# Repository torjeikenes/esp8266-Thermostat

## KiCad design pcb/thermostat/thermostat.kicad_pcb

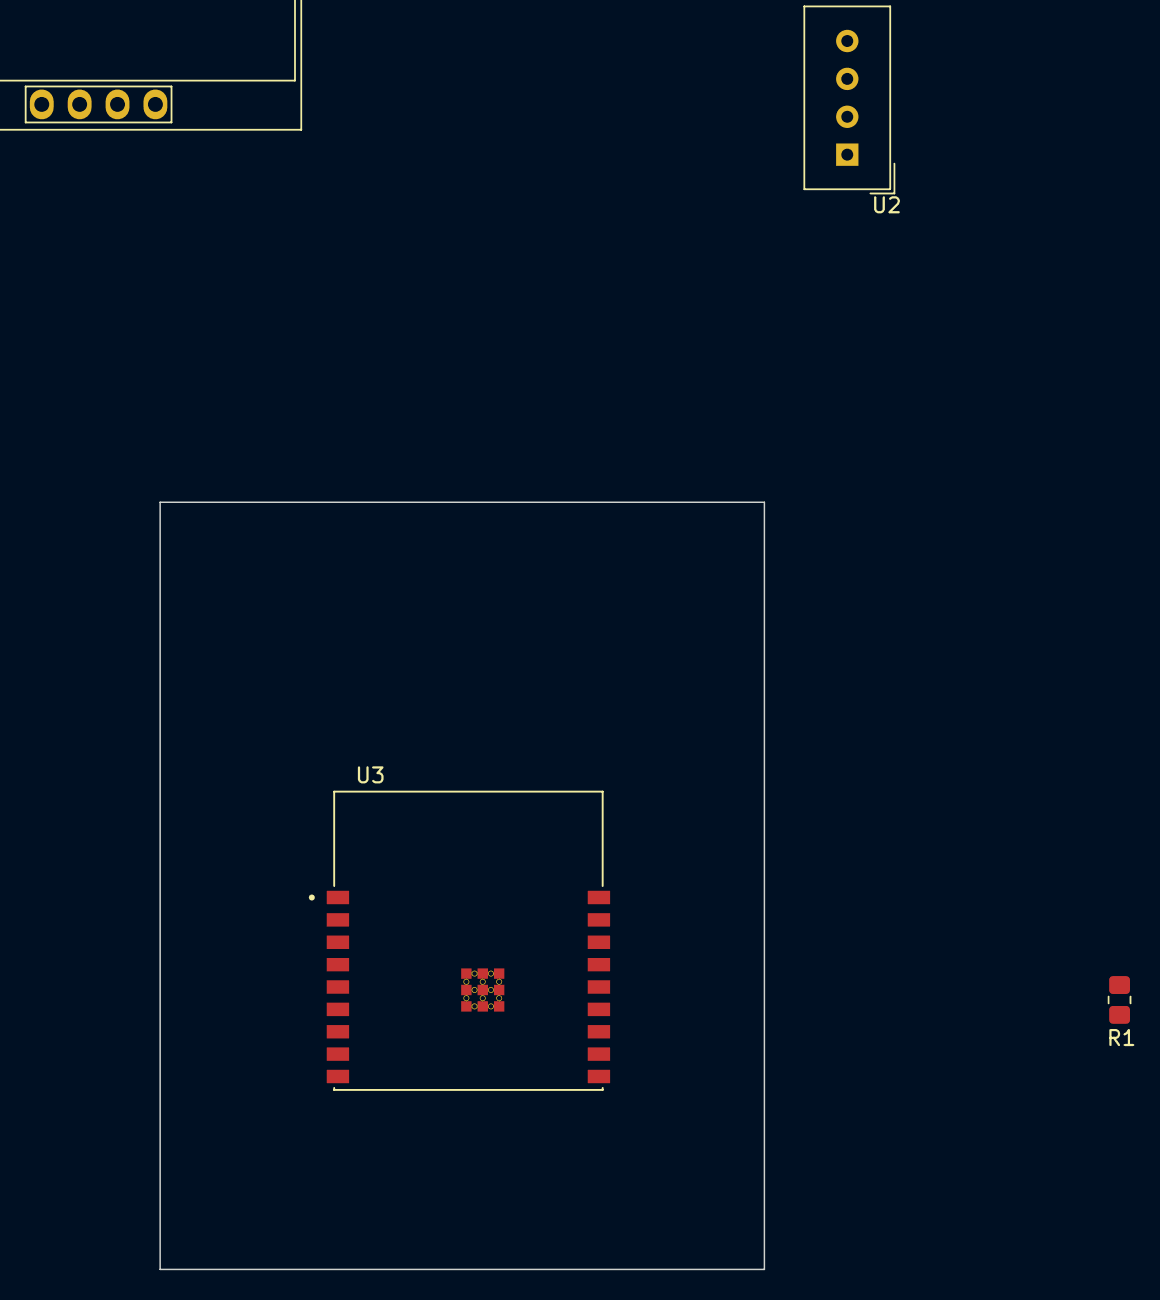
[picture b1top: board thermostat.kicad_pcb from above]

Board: 2 copper layers, 40.5 x 51.4 mm, 4 parts (0 on the bottom side), 5 nets, no tracks yet.

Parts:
Brd1: SSD1306; 128x64OLED
R1: 10k; R_0805_2012Metric_Pad1.20x1.40mm_HandSolder
U2: DHT11; Aosong_DHT11_5.5x12.0_P2.54mm
U3: ESP32-C3-WROOM-02-H4; MODULE_ESP32-C3-WROOM-02-H4

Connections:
+3V3: Brd1.2 (VCC), R1.1, U2.1 (VCC), U3.1 (3V3)
GND: Brd1.1 (GND), U2.4 (GND), U3.9 (GND), U3.19 (GND), U3.20 (GND), U3.21 (GND), U3.22 (GND), U3.23 (GND), U3.24 (GND), U3.25 (GND), U3.26 (GND), U3.27 (GND), U3.28 (GND), U3.29 (GND), U3.30 (GND), U3.31 (GND), U3.32 (GND), U3.33 (GND), U3.34 (GND), U3.35 (GND), U3.36 (GND), U3.37 (GND), U3.38 (GND), U3.39 (GND)
SCL: Brd1.3 (SCL), U3.6 (IO7)
SDA: Brd1.4 (SDA), U3.7 (IO8)
dhtData: R1.2, U2.2 (IO), U3.15 (IO3)

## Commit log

2022-11-01 Initial init
2022-11-01 Current temp and target temp shows on display
2022-11-01 Started on rotary encoder implementation
2022-11-02 Maybe fixed rotary encoder interrupt. Not tested
2022-11-02 Added pcb
2022-12-02 Ported to platformIO
2022-12-02 Added libraries
2022-12-04 added dependency
2022-12-08 Small fixes
2022-12-09 shows outside temperature
2022-12-10 changed encoder funciton
2023-09-06 Added esp32
